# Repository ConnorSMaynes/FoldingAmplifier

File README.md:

# FoldingAmplifier
1.778Vpp folding amplifier LTSpice simulation, KiCAD PCB design, and report on implementation results

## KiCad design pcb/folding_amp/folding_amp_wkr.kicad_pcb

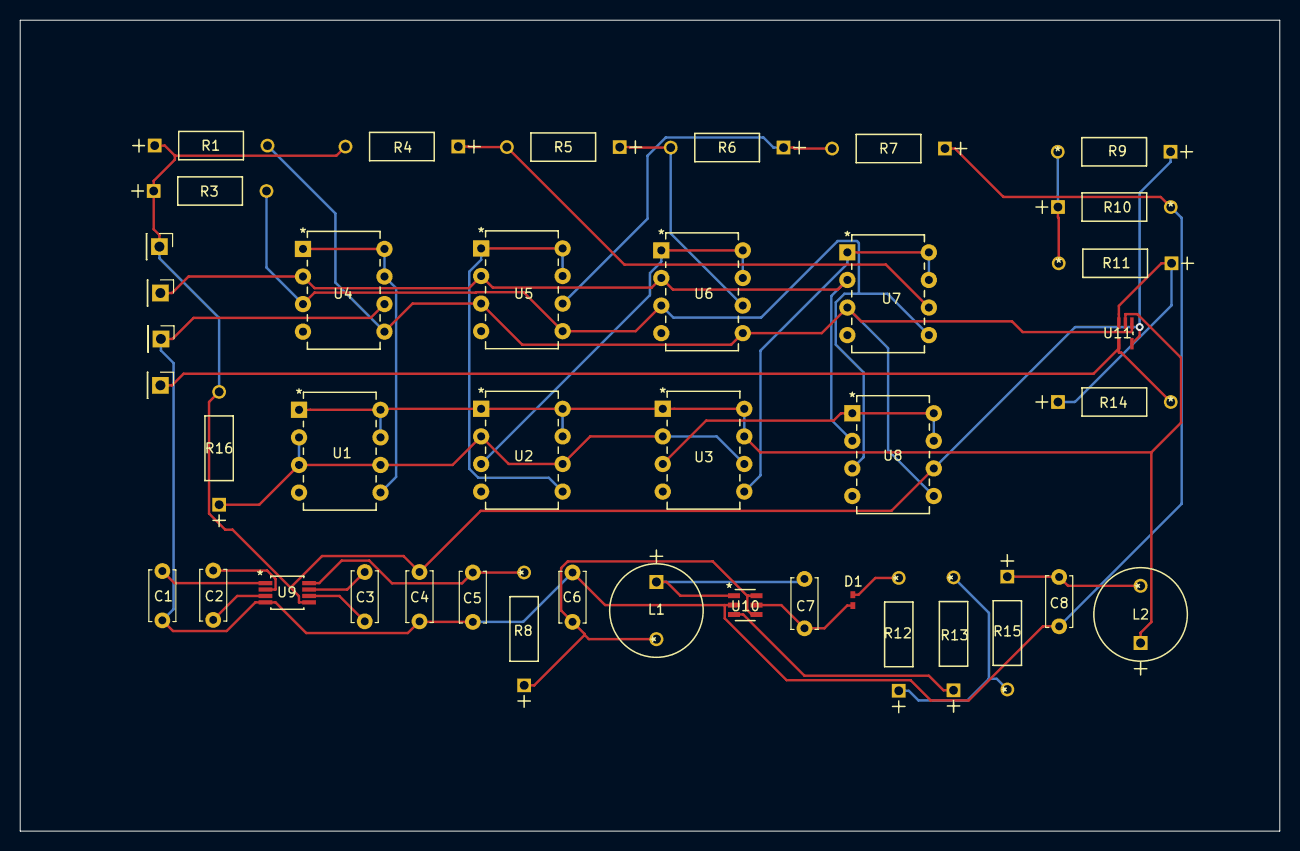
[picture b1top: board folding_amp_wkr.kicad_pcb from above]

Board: 2 copper layers, 127.6 x 82.2 mm, 41 parts (0 on the bottom side), 31 nets.

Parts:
C1, C4, C8: 10u; C_Disc_D5.0mm_W2.5mm_P5.00mm
C2, C3: 1u; C_Disc_D5.0mm_W2.5mm_P5.00mm
C5, C6: 4.7u; C_Disc_D5.0mm_W2.5mm_P5.00mm
C7: 270n; C_Disc_D5.0mm_W2.5mm_P5.00mm
D1: PMEG2005EB,115
J1, J2, J3, J4: Conn_01x01_Male; PinHeader_1x01_P2.54mm_Vertical
L1, L2: 10u; inductor
R1, R3: 3k; large_resistor
R4, R5, R6, R7: 1k; large_resistor
R8, R12: 10; large_resistor
R9: 620; large_resistor
R10: 510; large_resistor
R11: 10k; large_resistor
R13: 100k; large_resistor
R14: 130k; large_resistor
R15: 1; large_resistor
R16: 15k; large_resistor
U1, U2, U3, U4, U5, U6, U7, U8: ALD1101PAL
U9: LTC1502CMS8_3.3_PBF; LTC1502CMS8-3.3-PBF
U10: LT3483IS6_TRMPBF; LT3483IS6-TRMPBF
U11: TLV6001IDCKR

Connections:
/+Vref: C4.1, J2.1, R1.1, R3.1, R4.2, R9.1, R16.2, U8.6, U9.5, U11.5
/-Vref: L2.1, U1.1, U1.7, U1.8, U2.1, U2.7, U2.8, U3.1, U3.7, U3.8, U11.2
/I1: U3.3, U8.1, U8.7, U8.8
/I2: U3.5, U7.1, U7.7, U7.8
/I3: U2.3, U6.1, U6.7, U6.8
/I4: U2.5, U5.1, U5.7, U5.8
/I5: U1.5, U4.1, U4.7, U4.8
/V_Load_1: R3.2, U4.3, U5.5, U6.3, U7.5, U8.3
/V_Load_2: R1.2, U4.5, U5.3, U6.5, U7.3, U8.5, U11.1
/V_REF_2: R4.1, R5.2, U7.6
/V_REF_3: R5.1, R6.2, U6.6
/V_REF_4: R6.1, R7.2, U5.6
/Vgate: R16.1, U1.2, U1.3, U1.6, U2.2, U2.6, U3.2, U3.6
/Vin: J1.1, U4.2, U5.2, U6.2, U7.2, U8.2
/Vout: J3.1, R14.2, U11.4
GND: C1.2, C4.2, C5.2, C6.2, C8.2, J4.1, R7.1, R10.2, U4.6, U9.4, U10.2
unnamed: C1.1, U9.1
unnamed: C2.1, U9.2
unnamed: C2.2, U9.3
unnamed: C3.1, U9.7
unnamed: C3.2, U9.6
unnamed: C5.1, R8.2, U9.8
unnamed: C6.1, L1.2, R8.1, U10.4, U10.6
unnamed: C7.1, D1.1, U10.5
unnamed: C7.2, L1.1, U10.1
unnamed: C8.1, L2.2, R15.1
unnamed: D1.2, R12.2
unnamed: R9.2, R10.1, R11.2
unnamed: R11.1, R14.1, U11.3
unnamed: R12.1, R13.2, R15.2
unnamed: R13.1, U10.3

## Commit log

2018-12-06 init

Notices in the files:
parts and their libraries:
Copyright 2016 Accelerated Designs. All rights reserved.
